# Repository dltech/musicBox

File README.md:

# musicbox
A speex codec based musical box, functions:\
*lossy sound with adoptable quality\
*cheap chipset (bios spi flash and STM32 only)\
*10 types of pre recorded songs, which can be chosen using 10 buttons\
*uploading songs through usb\
*single battery supply (using dc-dc)\
*1W power amp\
*RGB disco led

This project is not released yet, but never will be closed.\
TODO:\
*speex narrowband decoding only build (ok)\
*protocol for uploading music files through usb-com(0%)\
*pc GUI for saving songs(0%)\
*tiny pcb 15x35mm (ok)

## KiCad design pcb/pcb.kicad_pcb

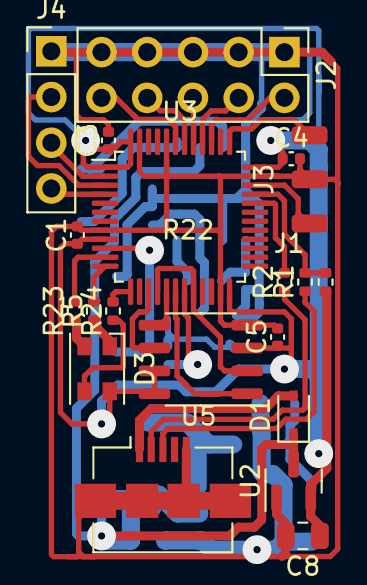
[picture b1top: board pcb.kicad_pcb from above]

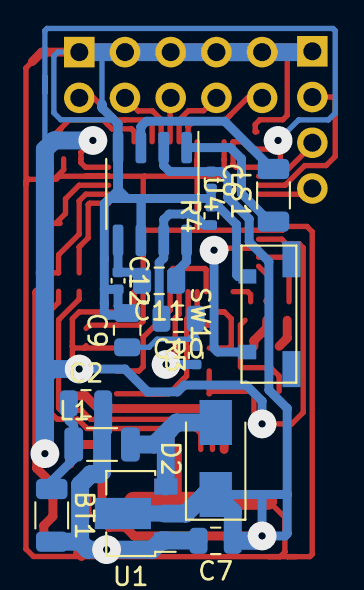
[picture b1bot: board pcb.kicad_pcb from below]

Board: 2 copper layers, 36 parts (16 on the bottom side), 38 nets.

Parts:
BT1: AAA; R_1206_3216Metric
C1, C3, C4, C5, C6, C12: 0.1uF; C_0402_1005Metric
C2, C7, C8, C11: 10uF; C_0805_2012Metric
C9, C10: 1uF; C_0805_2012Metric
D1: 1N5822; D_SOD-323
D2: 1N5822; D_SMA
D3: disco; LED_Cree-PLCC4_3.2x2.8mm_CCW
J1: upd_song; USB_Micro-B_Amphenol_10104110_Horizontal
J2: select; PinHeader_2x05_P2.54mm_Vertical
J3: swd; 3WIRE_PADS
J4: buttons; PinHeader_1x04_P2.54mm_Vertical
L1: 47uH; L_1206_3216Metric
LS1: Speaker; R_1206_3216Metric
R1, R2, R3, R5, R23, R24: 30; R_0402_1005Metric
R4, R22: 10k; R_0402_1005Metric
SW1: menu; smd_sw_ali
U1: ME2108A; SOT-89-3
U2: XC6206P333MR; SOT-23
U3: STM32F103C6Tx; LQFP-48_7x7mm_P0.5mm
U4: TDA2822; SO-8_3.9x4.9mm_P1.27mm
U5: AT25xxx; SO-8_3.9x4.9mm_P1.27mm

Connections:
+3.3V: C1.1, C3.1, C4.1, C5.1, C8.1, D3.4 (A), R22.1, U2.2 (VO), U3.1 (VBAT), U3.9 (VDDA), U3.24 (VDD), U3.36 (VDD), U3.48 (VDD), U5.3 (~WP), U5.7 (~HOLD), U5.8 (VCC)
+5V: C6.1, C7.1, D1.1 (K), D2.1 (K), U1.2 (OUT), U2.3 (VI), U4.2 (Vcc)
GND: BT1.2 (-), C1.2, C2.2, C3.2, C4.2, C5.2, C6.2, C7.2, C8.2, C9.2, C12.2, J1.5 (GND), J1.6 (Shield), J2.1, J2.3, J2.5, J2.7, J2.9, J3.2, J4.1, R4.2, SW1.1, U1.1 (Vss), U2.1 (GND), U3.8 (VSSA), U3.23 (VSS), U3.35 (VSS), U3.44 (BOOT0), U3.47 (VSS), U4.4 (GND), U4.6 (IN2+), U5.4 (GND)
unnamed: BT1.1 (+), C2.1, L1.1
unnamed: C9.1, C10.1, R3.2
unnamed: C10.2, R4.1, U4.7 (IN1+)
unnamed: C11.1, U4.8 (IN1-)
unnamed: C11.2, C12.1, U4.5 (IN2-)
unnamed: D1.2 (A), J1.1 (VBUS)
unnamed: D2.2 (A), L1.2, U1.3 (Lx)
unnamed: D3.1 (RK), R5.1
unnamed: D3.2 (GK), R23.1
unnamed: D3.3 (BK), R24.1
unnamed: J1.2 (D-), R2.1
unnamed: J1.3 (D+), R1.1
unnamed: J2.2, U3.39 (PB3)
unnamed: J2.4, U3.40 (PB4)
unnamed: J2.6, U3.41 (PB5)
unnamed: J2.8, U3.42 (PB6)
unnamed: J2.10, U3.43 (PB7)
unnamed: J3.1, U3.34 (PA13)
unnamed: J3.3, U3.37 (PA14)
unnamed: J4.3, U3.2 (PC13)
unnamed: J4.4, U3.4 (PC15)
unnamed: LS1.1, U4.1 (OUT1)
unnamed: LS1.2, U4.3 (OUT2)
unnamed: R2.2, U3.32 (PA11)
unnamed: R3.1, U3.19 (PB1)
unnamed: R5.2, U3.12 (PA2)
unnamed: R1.2, R22.2, U3.33 (PA12)
unnamed: R23.2, U3.11 (PA1)
unnamed: R24.2, U3.13 (PA3)
unnamed: SW1.2, U3.10 (PA0)
unnamed: J4.2, U3.3 (PC14)
unnamed: U3.15 (PA5), U5.6 (SCK)
unnamed: U3.17 (PA7), U5.5 (MOSI)
unnamed: U3.18 (PB0), U5.1 (~CS)
unnamed: U3.16 (PA6), U3.20 (PB2), U5.2 (MISO)

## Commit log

2022-11-15 libs obtained, example of quality
2022-11-15 narrowband decoder only libraries found
2022-11-15 readme with todo
2022-11-29 speex init
2022-11-29 types of speex
2022-11-29 filters.c almost compiled
2022-11-30 all subfunctions are compiled
2022-11-30 compiled, RAM error
2022-11-30 it builds!
2022-12-01 pcb almost compl
2022-12-01 readme
2022-12-02 pcb ok
2022-12-02 ex_8000bitps.wav
